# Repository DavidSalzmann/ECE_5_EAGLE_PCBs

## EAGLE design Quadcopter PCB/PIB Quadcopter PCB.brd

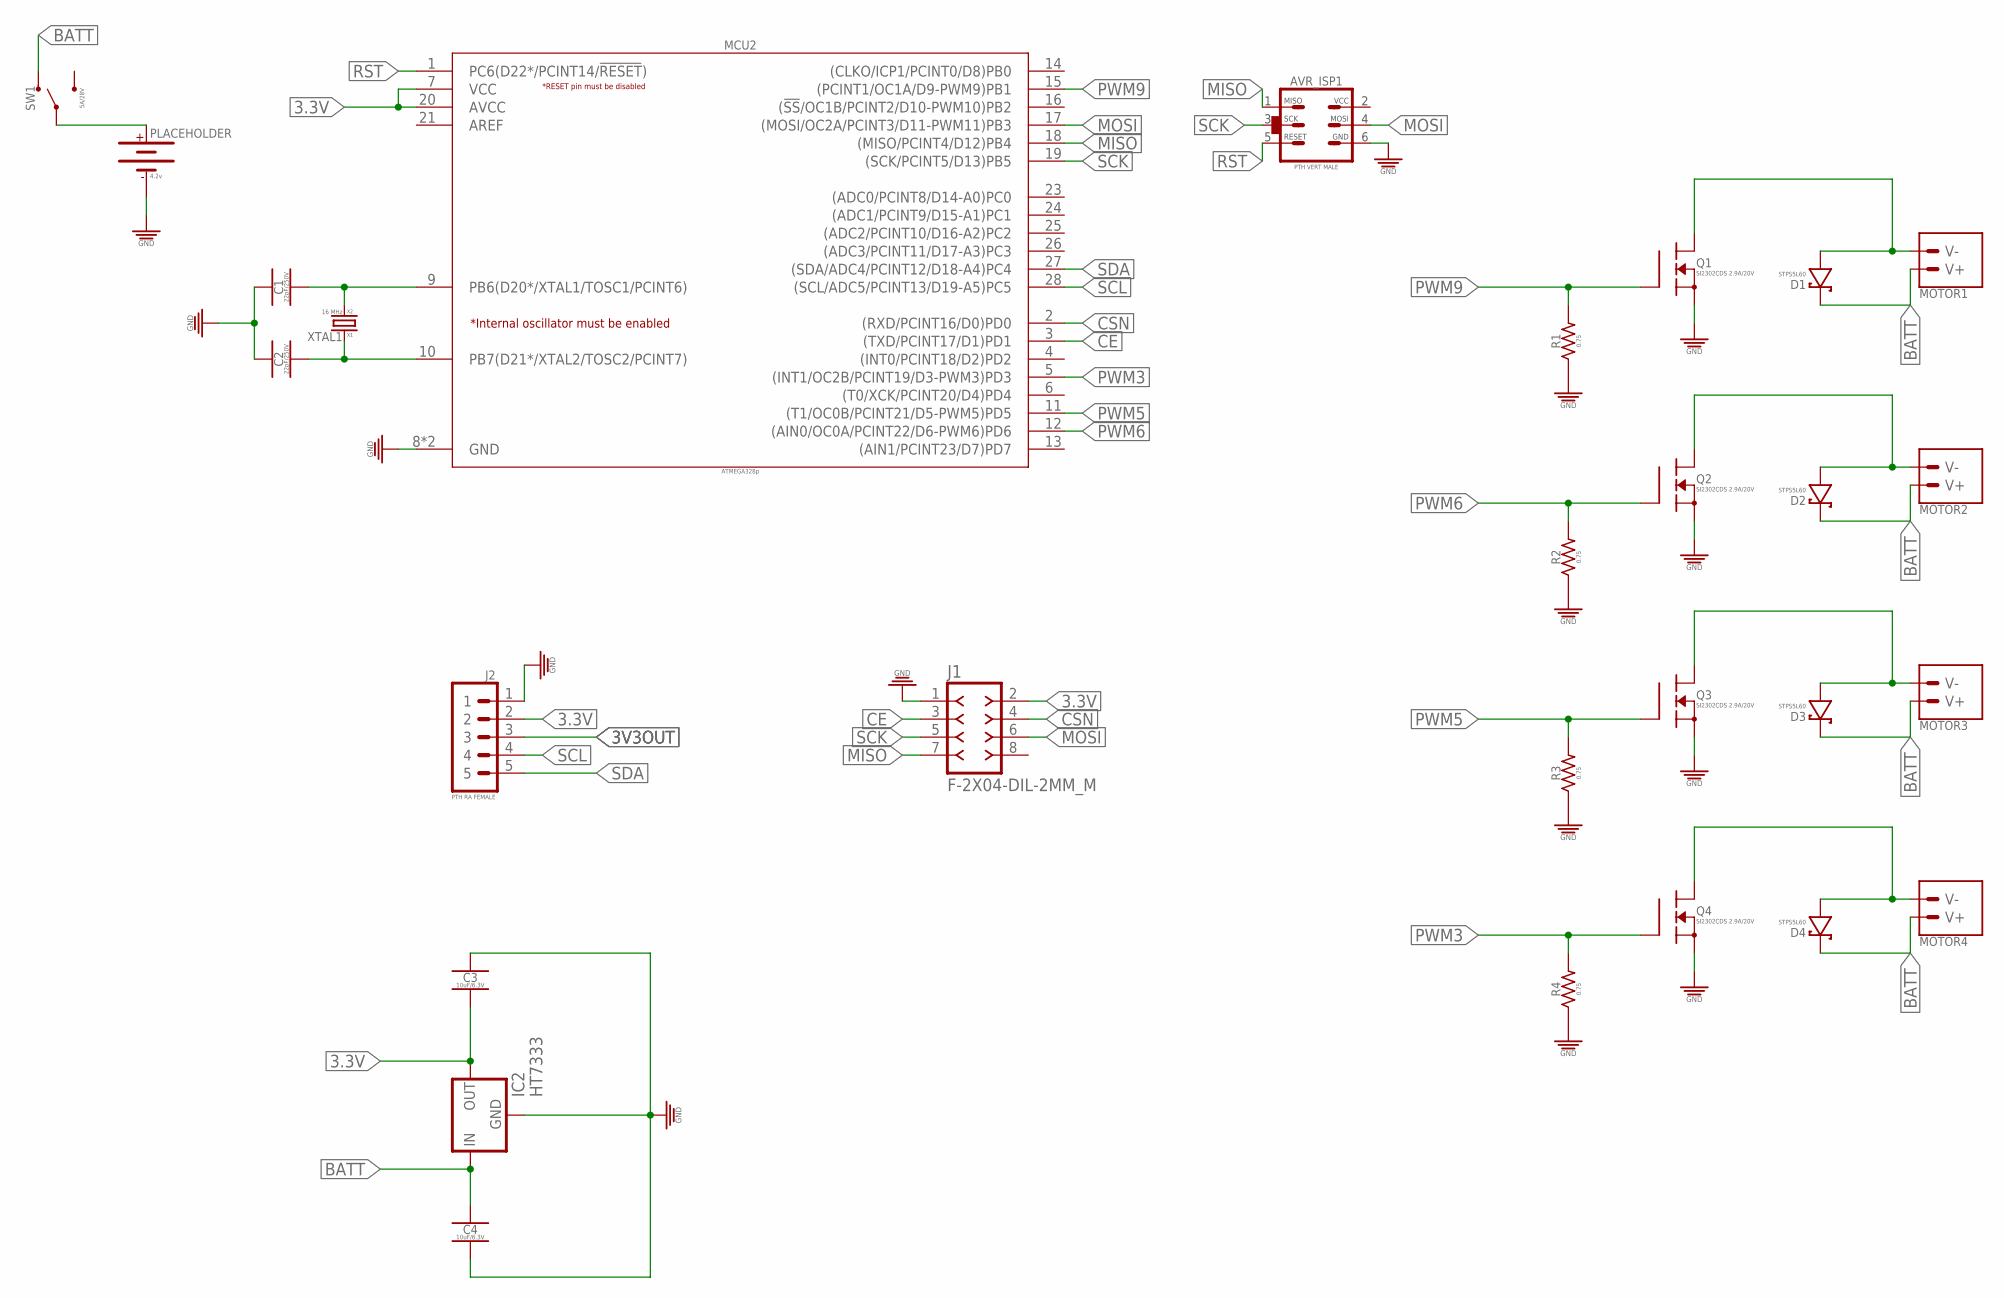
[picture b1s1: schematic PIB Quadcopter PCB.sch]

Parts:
AVR_ISP1: PTH VERT MALE; HDRV6W64P254_2X3_762X483X838B_AVR-ISP
C1, C2: 22pF/250V; CAPC1608X95
C3, C4: 10uF/6.3V; CAPC1005X55_SMD-0402
D1, D2, D3, D4: STPS5L60; D0-201AD
IC2: HT7333; SOT-89
J1: F-2X04-DIL-2MM_M; DIL-2MM-2X04_M
J2: PTH RA FEMALE; HDRRAR5W60P254_1X5_1320X850X274B
MCU2: ATMEGA328p; DIP762W53P254L3467H472Q28B
MOTOR1, MOTOR2, MOTOR3, MOTOR4: MOTOR_PADSPTH; CONNECTOR_MOTOR
PLACEHOLDER: 4.2v; BATTERY_MOLEX-89400_VERT_PITCH-2MM
Q1, Q2, Q3, Q4: SI2302CDS 2.9A/20V; SOT95P287X112-3
R1, R2, R3, R4: 0.75; RESC1608X65_SMD-0603
SW1: 5A/28V; SW_TOGGLE_SPDT_5A-28V_13L-7W
XTAL1: 16 MHz; HC-49/US

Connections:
3.3V: C3.2, IC2.1 (OUT), J1.2, J2.2, MCU2.7 (VCC), MCU2.20 (AVCC)
3V3OUT: J2.3
BATT: C4.1, D1.K (A), D2.K (A), D3.K (A), D4.K (A), IC2.3 (IN), IC2.4 (IN), MOTOR1.+ (V+), MOTOR2.+ (V+), MOTOR3.+ (V+), MOTOR4.+ (V+), SW1.S1
CE: J1.3, MCU2.3 ((TXD/PCINT17/D1)PD1)
CSN: J1.4, MCU2.2 ((RXD/PCINT16/D0)PD0)
GND: AVR_ISP1.GND, C1.1, C2.1, C3.1, C4.2, IC2.2 (GND), J1.1, J2.1, MCU2.8 (GND), MCU2.22 (GND), PLACEHOLDER.-, Q1.2 (S), Q2.2 (S), Q3.2 (S), Q4.2 (S), R1.1, R2.1, R3.1, R4.1
MISO: AVR_ISP1.MISO, J1.7, MCU2.18 ((MISO/PCINT4/D12)PB4)
MOSI: AVR_ISP1.MOSI, J1.6, MCU2.17 ((MOSI/OC2A/PCINT3/D11-PWM11)PB3)
unnamed: D2.A (K), MOTOR2.- (V-), Q2.3 (D)
unnamed: D3.A (K), MOTOR3.- (V-), Q3.3 (D)
unnamed: D4.A (K), MOTOR4.- (V-), Q4.3 (D)
unnamed: C1.2, MCU2.9 (PB6(D20*/XTAL1/TOSC1/PCINT6)), XTAL1.P$2 (XTAL2)
unnamed: C2.2, MCU2.10 (PB7(D21*/XTAL2/TOSC2/PCINT7)), XTAL1.P$1 (XTAL1)
unnamed: D1.A (K), MOTOR1.- (V-), Q1.3 (D)
unnamed: PLACEHOLDER.+, SW1.P
PWM3: MCU2.5 ((INT1/OC2B/PCINT19/D3-PWM3)PD3), Q4.1 (G), R4.2
PWM5: MCU2.11 ((T1/OC0B/PCINT21/D5-PWM5)PD5), Q3.1 (G), R3.2
PWM6: MCU2.12 ((AIN0/OC0A/PCINT22/D6-PWM6)PD6), Q2.1 (G), R2.2
PWM9: MCU2.15 ((PCINT1/OC1A/D9-PWM9)PB1), Q1.1 (G), R1.2
RST: AVR_ISP1.RESET, MCU2.1 (PC6(D22*/PCINT14/!RESET!))
SCK: AVR_ISP1.SCK, J1.5, MCU2.19 ((SCK/PCINT5/D13)PB5)
SCL: J2.4, MCU2.28 ((SCL/ADC5/PCINT13/D19-A5)PC5)
SDA: J2.5, MCU2.27 ((SDA/ADC4/PCINT12/D18-A4)PC4)

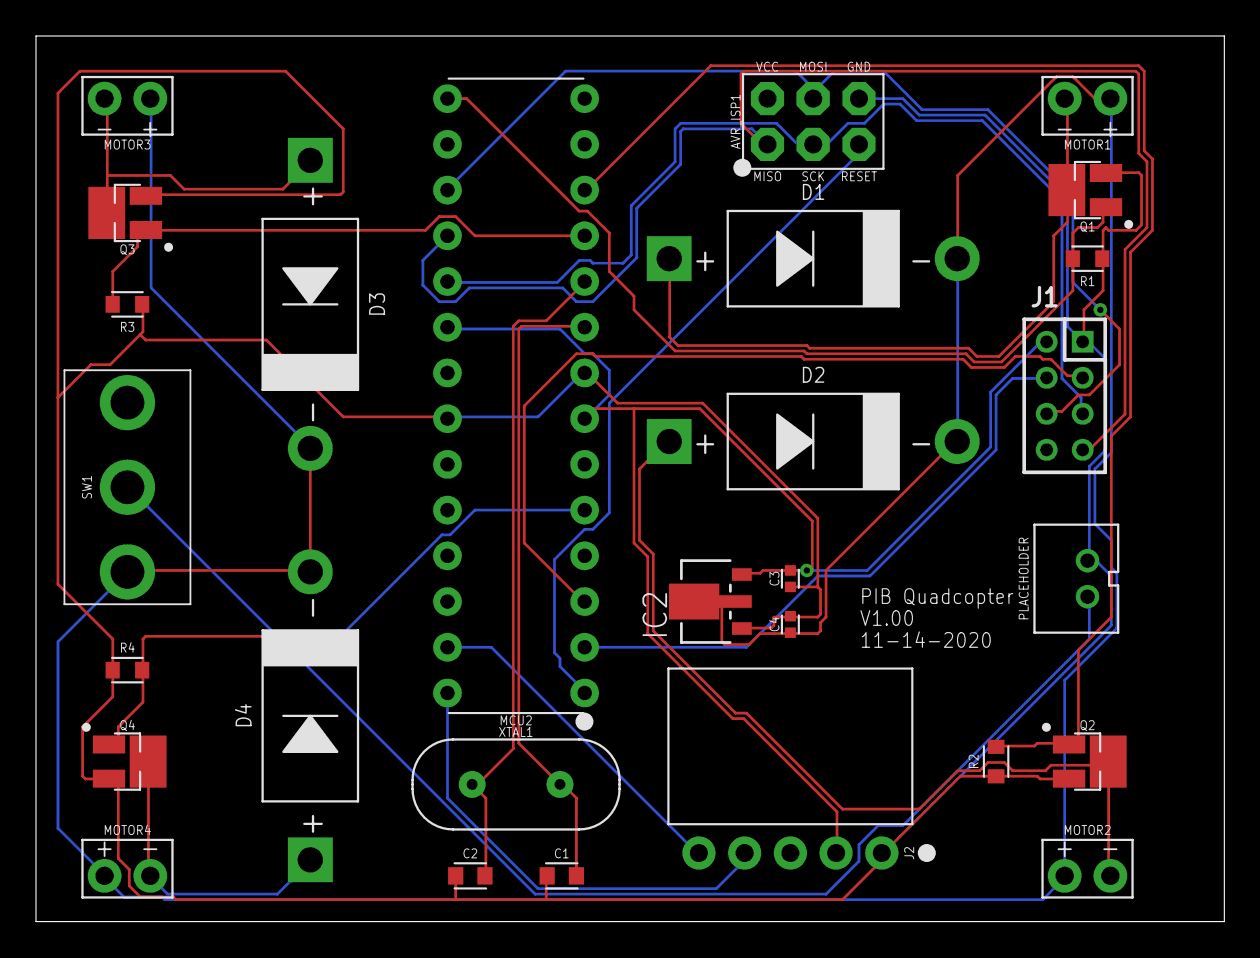
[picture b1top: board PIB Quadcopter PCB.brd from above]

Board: 2 copper layers, 66.0 x 49.2 mm, 28 parts (0 on the bottom side), 22 nets.

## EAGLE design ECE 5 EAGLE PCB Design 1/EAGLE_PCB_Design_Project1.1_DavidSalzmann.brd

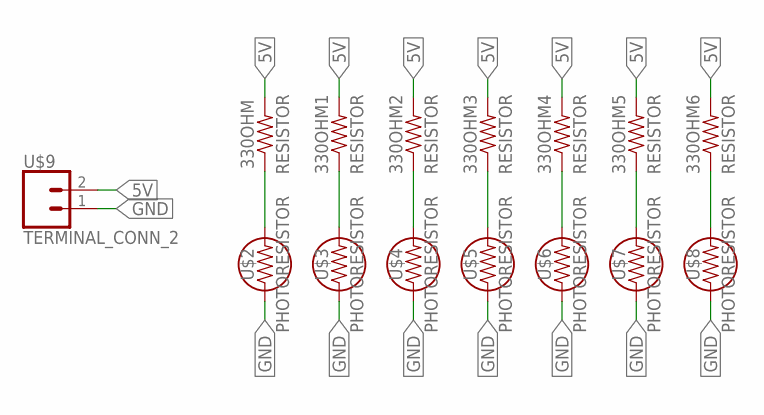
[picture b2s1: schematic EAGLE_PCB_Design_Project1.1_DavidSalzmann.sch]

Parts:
330OHM, 330OHM1, 330OHM2, 330OHM3, 330OHM4, 330OHM5, 330OHM6: RESISTOR
U$2, U$3, U$4, U$5, U$6, U$7, U$8: PHOTORESISTOR
U$9: TERMINAL_CONN_2

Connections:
5V: 330OHM.2, 330OHM1.2, 330OHM2.2, 330OHM3.2, 330OHM4.2, 330OHM5.2, 330OHM6.2, U$9.2
GND: U$2.P$1 (1), U$3.P$1 (1), U$4.P$1 (1), U$5.P$1 (1), U$6.P$1 (1), U$7.P$1 (1), U$8.P$1 (1), U$9.1
unnamed: 330OHM.1, U$2.P$2 (2)
unnamed: 330OHM1.1, U$3.P$2 (2)
unnamed: 330OHM2.1, U$4.P$2 (2)
unnamed: 330OHM3.1, U$5.P$2 (2)
unnamed: 330OHM4.1, U$6.P$2 (2)
unnamed: 330OHM5.1, U$7.P$2 (2)
unnamed: 330OHM6.1, U$8.P$2 (2)

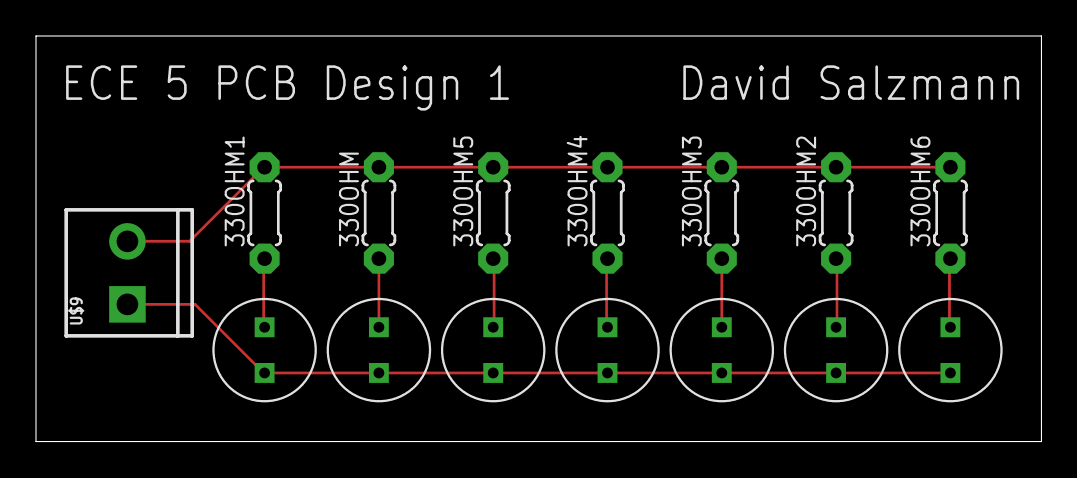
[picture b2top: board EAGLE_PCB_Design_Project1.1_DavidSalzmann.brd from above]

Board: 2 copper layers, 55.9 x 22.5 mm, 15 parts (0 on the bottom side), 9 nets.

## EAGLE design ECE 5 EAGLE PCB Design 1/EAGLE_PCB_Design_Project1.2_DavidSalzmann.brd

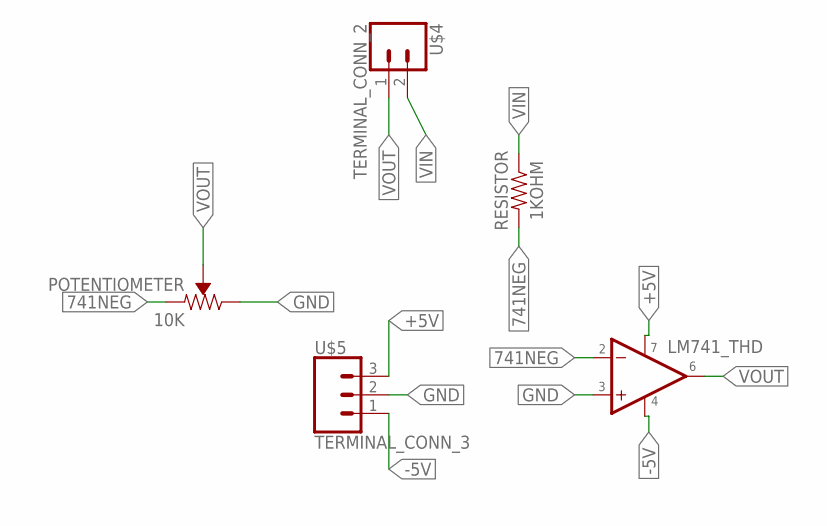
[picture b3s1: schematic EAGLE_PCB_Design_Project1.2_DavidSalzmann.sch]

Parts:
1KOHM: RESISTOR
10K: POTENTIOMETER
U$1: IC-LM741
U$4: TERMINAL_CONN_2
U$5: TERMINAL_CONN_3; TERMINAL-CONN_3

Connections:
741NEG: 1KOHM.2, 10K.3 (CCW), U$1.2 (-IN)
+5V: U$1.7, U$5.3
-5V: U$1.4, U$5.1
GND: 10K.2 (CW), U$1.3 (+IN), U$5.2
VIN: 1KOHM.1, U$4.2
VOUT: 10K.1 (WIPER), U$1.6 (OUT), U$4.1

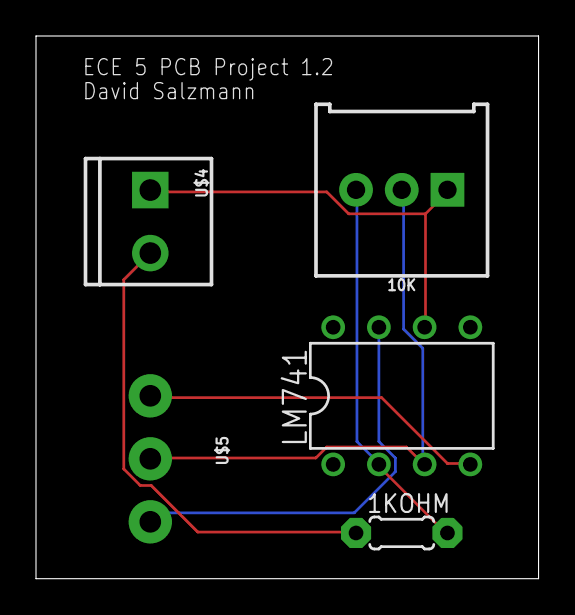
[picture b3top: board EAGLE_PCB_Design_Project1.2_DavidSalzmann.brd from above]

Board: 2 copper layers, 27.9 x 30.1 mm, 5 parts (0 on the bottom side), 6 nets.

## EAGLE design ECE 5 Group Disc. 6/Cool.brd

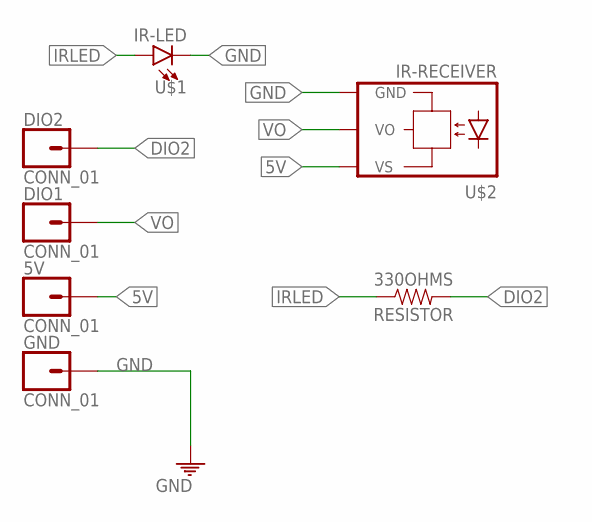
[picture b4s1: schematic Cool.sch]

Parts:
5V: CONN_01; 1X01
330OHMS: RESISTOR; AXIAL-0.3
DIO1, DIO2: CONN_01; 1X01
GND: CONN_01; 1X01
U$1: IR-LED; LED_5MM
U$2: IR-RECEIVER; TSOP17_TB1

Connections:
5V: 5V.1, U$2.VS
DIO2: 330OHMS.P$2 (2), DIO2.1
GND: GND.1, U$1.K (C), U$2.GND
IRLED: 330OHMS.P$1 (1), U$1.A
VO: DIO1.1, U$2.VO

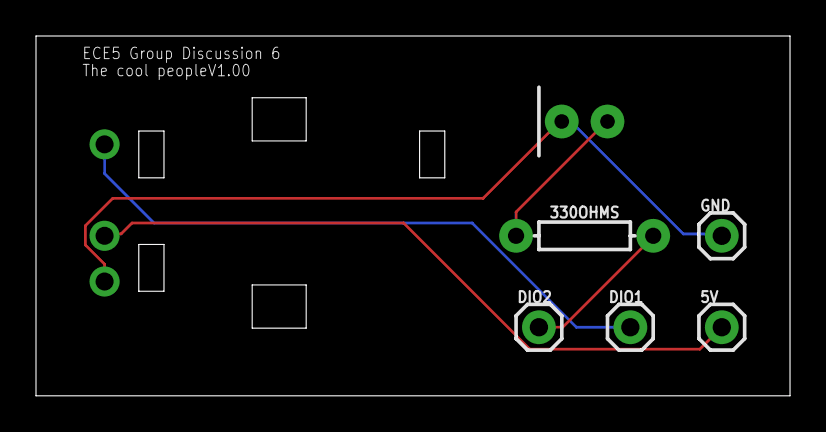
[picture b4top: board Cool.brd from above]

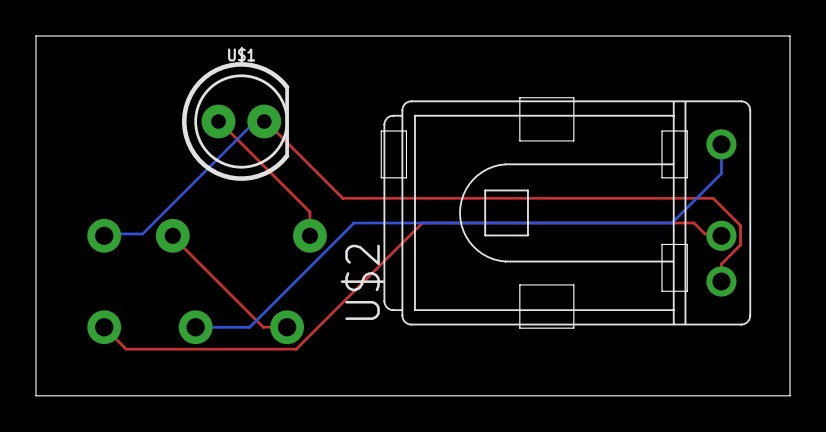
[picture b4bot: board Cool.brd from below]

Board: 2 copper layers, 41.9 x 20.0 mm, 7 parts (2 on the bottom side), 5 nets.

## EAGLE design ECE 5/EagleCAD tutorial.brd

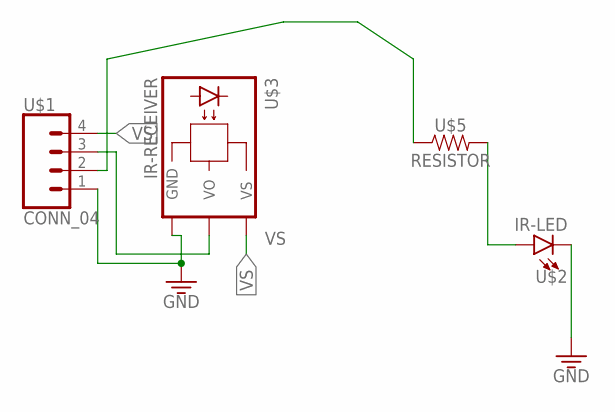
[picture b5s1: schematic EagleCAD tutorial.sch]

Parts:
U$1: CONN_04; MOLEX-1X4
U$2: IR-LED; LED_5MM
U$3: IR-RECEIVER; TSOP17_TB1
U$5: RESISTOR; AXIAL-0.3

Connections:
3.3V: U$1.1, U$2.K (C), U$3.GND
unnamed: U$2.A, U$5.P$2 (2)
unnamed: U$1.3, U$3.VO
unnamed: U$1.2, U$5.P$1 (1)
VS: U$1.4, U$3.VS

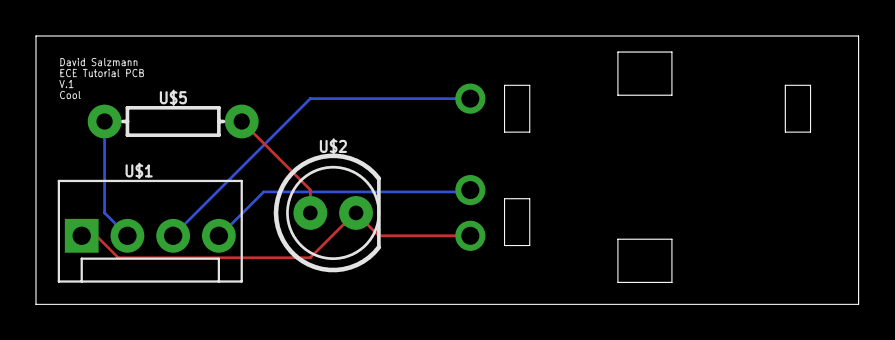
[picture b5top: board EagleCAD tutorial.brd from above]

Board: 2 copper layers, 45.7 x 14.9 mm, 4 parts (1 on the bottom side), 5 nets.

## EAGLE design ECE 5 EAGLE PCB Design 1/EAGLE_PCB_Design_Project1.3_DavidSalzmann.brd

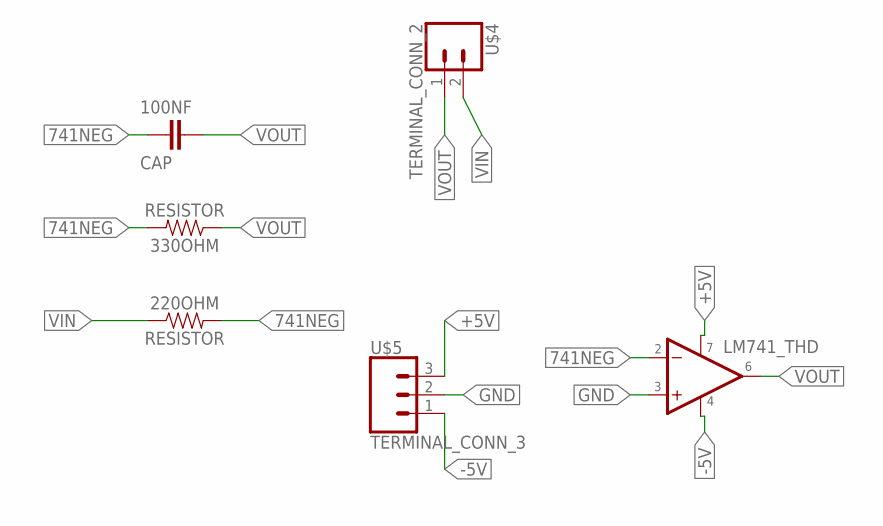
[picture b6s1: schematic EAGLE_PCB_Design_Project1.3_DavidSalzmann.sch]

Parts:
100NF: CAP; CAP-TH
220OHM, 330OHM: RESISTOR
U$1: IC-LM741
U$4: TERMINAL_CONN_2
U$5: TERMINAL_CONN_3; TERMINAL-CONN_3

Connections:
741NEG: 100NF.1, 220OHM.2, 330OHM.2, U$1.2 (-IN)
+5V: U$1.7, U$5.3
-5V: U$1.4, U$5.1
GND: U$1.3 (+IN), U$5.2
VIN: 220OHM.1, U$4.2
VOUT: 100NF.2, 330OHM.1, U$1.6 (OUT), U$4.1

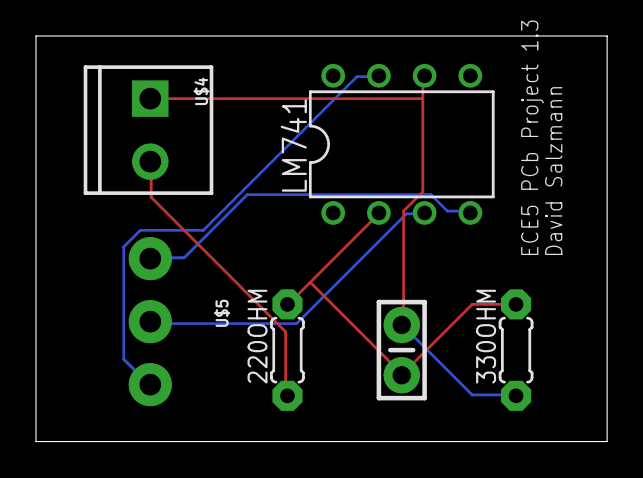
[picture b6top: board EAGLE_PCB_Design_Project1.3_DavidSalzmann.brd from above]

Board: 2 copper layers, 31.7 x 22.5 mm, 6 parts (0 on the bottom side), 6 nets.

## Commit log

2024-01-19 Initial FIle Upload

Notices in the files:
parts and their libraries:
con-headers-jp: Copyright (C) 2008, Bob Starr
